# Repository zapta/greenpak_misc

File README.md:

# GreenPAKs
Everything related to Renesas GreenPAK programable logic devices.

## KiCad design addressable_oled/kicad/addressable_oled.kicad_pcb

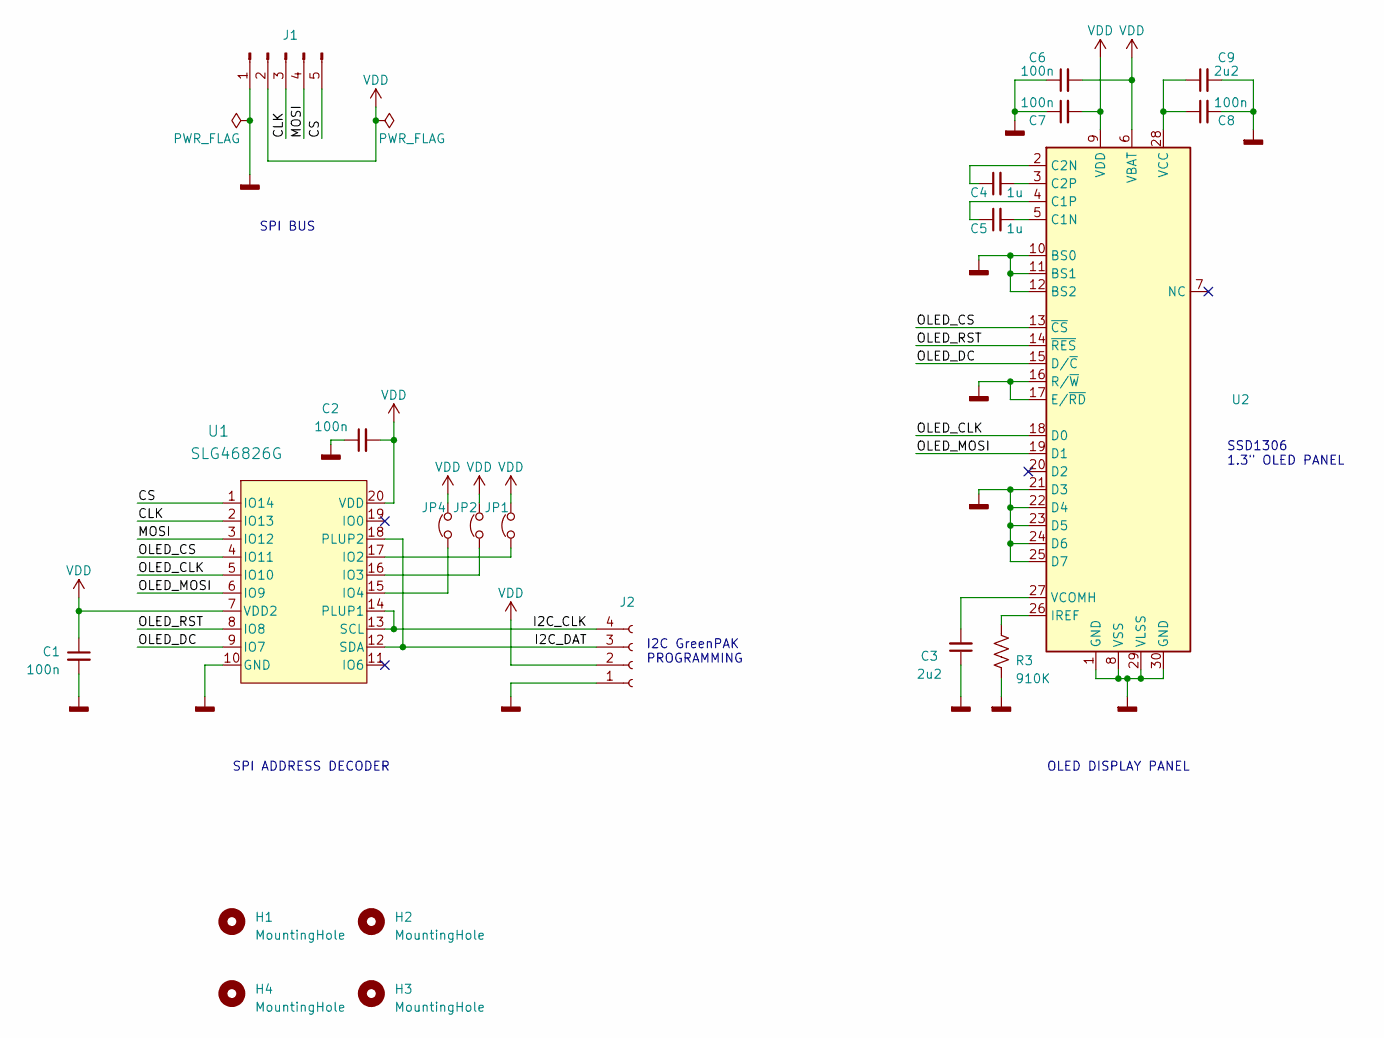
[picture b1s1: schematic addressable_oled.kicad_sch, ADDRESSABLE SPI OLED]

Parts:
C1, C2, C6, C7, C8: 100n; C_0603_1608Metric
C3, C9: 2u2; C_0603_1608Metric
C4, C5: 1u; C_0603_1608Metric
H1, H2, H3, H4: MountingHole
J1: Conn_01x05_Pin; PinHeader_1x05_P2.54mm_Vertical
J2: Conn_01x03_Socket; PinHeader_1x04_P2.54mm_Vertical
JP1, JP2, JP4: Jumper_2_Open; SolderJumper-2_P1.3mm_Open_Pad1.0x1.5mm
R3: 910K; R_0603_1608Metric
U1: SLG46826G; TSSOP20_MO-220_WECE_REN
U2: OLED-128O064D

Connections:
/CLK: J1.3, U1.2 (IO13)
/CS: J1.5, U1.1 (IO14)
/I2C_CLK: J2.4, U1.13 (SCL), U1.14 (PLUP1)
/I2C_DAT: J2.3, U1.12 (SDA), U1.18 (PLUP2)
/MOSI: J1.4, U1.3 (IO12)
/OLED_CLK: U1.5 (IO10), U2.18 (D0)
/OLED_CS: U1.4 (IO11), U2.13 (~CS)
/OLED_DC: U1.9 (IO7), U2.15 (D/~C)
/OLED_MOSI: U1.6 (IO9), U2.19 (D1)
/OLED_RST: U1.8 (IO8), U2.14 (~RES)
GND: C1.2, C2.1, C3.1, C6.1, C7.1, C8.2, C9.2, J1.1, J2.1, R3.2, U1.10 (GND), U2.1 (GND), U2.8 (VSS), U2.10 (BS0), U2.11 (BS1), U2.12 (BS2), U2.16 (R/~W), U2.17 (E/~RD), U2.21 (D3), U2.22 (D4), U2.23 (D5), U2.24 (D6), U2.25 (D7), U2.29 (VLSS), U2.30 (GND)
unnamed: JP1.1, U1.17 (IO2)
unnamed: JP2.1, U1.16 (IO3)
unnamed: JP4.1, U1.15 (IO4)
unnamed: C5.2, U2.5 (C1N)
unnamed: C5.1, U2.4 (C1P)
unnamed: C4.1, U2.2 (C2N)
unnamed: C4.2, U2.3 (C2P)
unnamed: R3.1, U2.26 (IREF)
unnamed: C8.1, C9.1, U2.28 (VCC)
unnamed: C3.2, U2.27 (VCOMH)
VDD: C1.1, C2.2, C6.2, C7.2, J1.2, J2.2, JP1.2, JP2.2, JP4.2, U1.7 (VDD2), U1.20 (VDD), U2.6 (VBAT), U2.9 (VDD)

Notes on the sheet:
SSD1306 1.3" OLED PANEL
I2C GreenPAK PROGRAMMING
SPI BUS
OLED DISPLAY PANEL
SPI ADDRESS DECODER

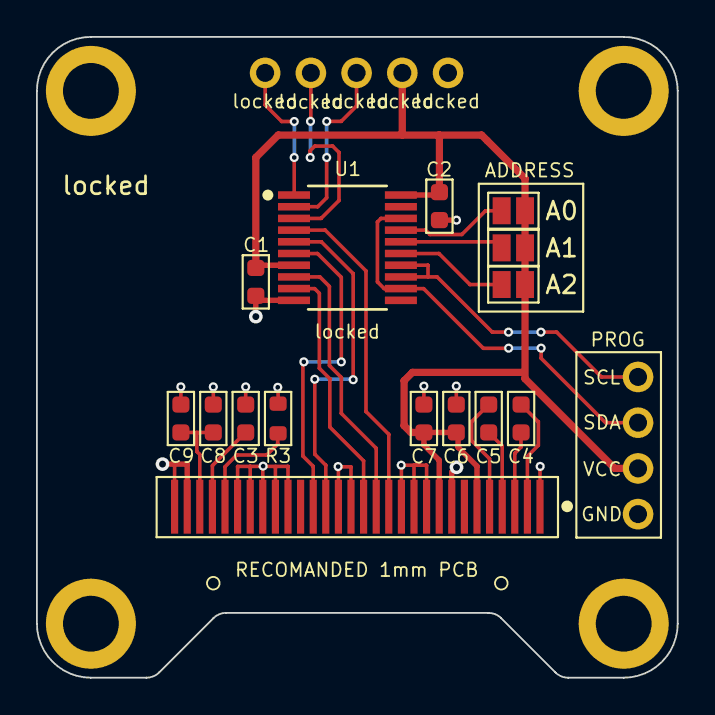
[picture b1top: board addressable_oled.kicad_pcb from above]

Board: 2 copper layers, 35.6 x 35.6 mm, 21 parts (0 on the bottom side), 22 nets.

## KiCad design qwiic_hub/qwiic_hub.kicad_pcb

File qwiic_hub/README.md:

# QWIIC I2C Hub

This little board provides a 1 to 4 fanout of QWIIC (I2C) connectors and allow to connect together multiple QWIIC boards such as the GreenPAK SMD adapters.

Item | Value | Comments
---|---|---
J1  |JST SH 1.0mm 4 Pos horizontal SMD | QWIIC input, from master.
J2- J5 |JST SH 1.0mm 4 Pos vertical SMD | QWIIC outputs, to slaves.
LED | Green LED  0603| Power indicator.
R | 3K - 7K 0603 resistor | LED current limiter.

<br>

<br>

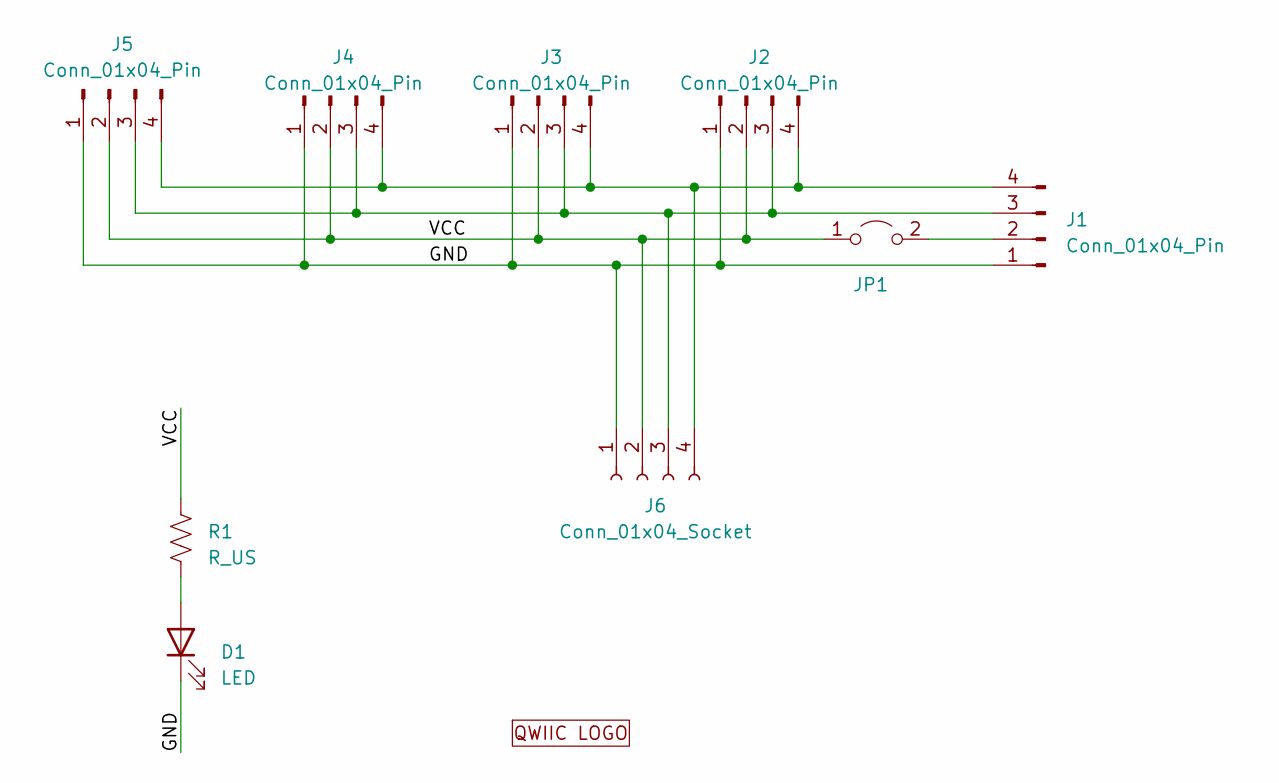
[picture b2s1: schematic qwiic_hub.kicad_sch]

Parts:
D1: LED; LED_0603_1608Metric
J1: Conn_01x04_Pin; JST_SH_SM04B-SRSS-TB_1x04-1MP_P1.00mm_Horizontal
J2, J3, J4, J5: Conn_01x04_Pin; JST_SH_BM04B-SRSS-TB_1x04-1MP_P1.00mm_Vertical
J6: Conn_01x04_Socket; PinHeader_1x04_P2.54mm_Vertical
JP1: Jumper_2_Open; SolderJumper-2_P1.3mm_Open_Pad1.0x1.5mm
R1: R_US; R_0402_1005Metric_Pad0.72x0.64mm_HandSolder
X1: QWIIC Logo; QWIIC_logo_10mm

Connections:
/GND: D1.1 (K), J1.1, J2.1, J3.1, J4.1, J5.1, J6.1
/VCC: J2.2, J3.2, J4.2, J5.2, J6.2, JP1.1 (A), R1.1
unnamed: D1.2 (A), R1.2
unnamed: J1.2, JP1.2 (B)
unnamed: J1.3, J2.3, J3.3, J4.3, J5.3, J6.3
unnamed: J1.4, J2.4, J3.4, J4.4, J5.4, J6.4

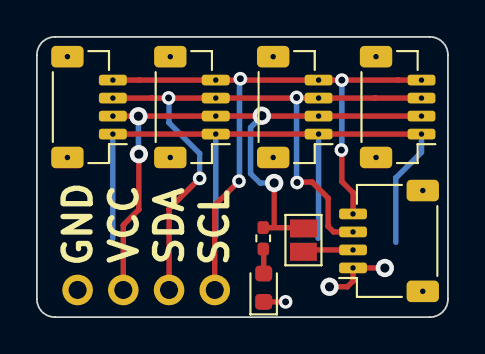
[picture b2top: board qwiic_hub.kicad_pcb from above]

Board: 2 copper layers, 22.8 x 15.6 mm, 10 parts (1 on the bottom side), 6 nets.

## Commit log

2023-12-01 Initial kicad version of smd_adapters. Needs cleanup.
2023-12-01 Cleaned up the GreenPAK TSSOP-20 smd adapter
2023-12-01 Added a sample design of an SPI address decoder.
2023-12-01 Renamed the smd adapters project.
2023-12-01 Cleaned up smd adapters directories.
2023-12-01 Fixed footprint library alias name.
2023-12-02 Completed the STQFN-24 greenpak smd adapter.
2023-12-02 Added pinout work in progress.
2023-12-02 Tweaked internal pullup/down resistors. Changed part number in pinout diagram to have the G extension.
2023-12-02 More progress on the TSQFN-20 smd adapter.
2023-12-03 More progress on the QFN-20 smd adapter.
2023-12-03 Completed the greenpak stqfn20 smd adapter.
2023-12-04 Adjusted the greenpak smd adaptres. Generated gerbers.
2023-12-04 Cleaned up greenpak smd adapters
2023-12-04 Updated greenpak smd adapter .png.
2023-12-04 Added gating of SCLK and MOSI
2023-12-05 Added a simple circuit for the glitch discussion.
2023-12-05 Added WaveDrop timing diagrams.
2023-12-06 Added pinout in png format.
2023-12-06 Renamed wavedrom files to .json.
2023-12-06 Tweaked timing diagrams.
2023-12-06 Added a readme file for the addressable SPI example.
2023-12-06 Tweaked readme.md.
2023-12-06 Fixed image reference in readme.md.
2023-12-06 Minor teadme.md fix.
2023-12-06 Minor readme.md tweak.
2023-12-06 MOved the addressable SPI directory.
2023-12-06 Tweaked readme.md
2023-12-06 Deleted unused images.
2023-12-06 Added a block diagram.
2023-12-06 MOSI out is not Z when CS_OUT is not active.
2023-12-06 Unify the timing diagrams.
2023-12-06 Changed the schematic from PNG to SVG.
2023-12-06 Flushing greenpak design changes.
2023-12-09 Added a blinky example
2023-12-09 Flushing blinky
2023-12-09 Renamed old blinky
2023-12-09 Added a blinky for the proper IC.
2023-12-10 Updated blinky files.
2023-12-10 Added docs directory
2023-12-10 Added pullup resistors to I2C signals.
2023-12-10 Changed i2C pullup resistors to 100k.
2023-12-10 Added a i2cdriver python skeleton
2023-12-10 Added user manual doc of the i2cmini
2023-12-10 Had progress on the i2C tool.
2023-12-11 Added a memory write method.
2023-12-11 Basic programming functionality is working.
2023-12-11 Cleaned up comments.
2023-12-11 Added two datasheets.
2023-12-11 Added test data file.
2023-12-11 Added functions to read/write config files.
2023-12-11 Updated programming capture file
2023-12-11 Added a workaround for reserved NVM bits and a method to reset the device.
2023-12-11 Renamed a directory
2023-12-11 Added better handling of non writeable NVM page.
2023-12-11 Cleaned up the operation waiting logic.
2023-12-11 Added method to scan the bus for devices.
2023-12-13 Skeleton for i2c pico.
2023-12-17 Added files for testing.
2023-12-17 Added code to dump generated bits.
2023-12-17 Added gitignore
2023-12-17 Consolidate doc directories
2023-12-19 Work in progress.
2023-12-20 Arduino serial bootloader works.
2023-12-20 Set up a skeleton with basic serial i/o.
2023-12-20 More progress with the pico i2c.
2023-12-20 More tweaks
2023-12-20 Deleted unused hidden arduino files.
2023-12-20 Dummy change for testing.
2023-12-21 Switched to the standard Arduino core.
2023-12-21 Cleaned up and added INFO command.
2023-12-21 Fixed a device address handling.
2023-12-22 Updated gitattributes.
2023-12-22 Added lib dependency on tinyusb
2023-12-22 Cleaned up old configuration.
2023-12-22 Added RPI Pico resources.
2023-12-22 Updated the Arduino driver installation instructions.
2023-12-22 Updated the installation notes.
2023-12-22 Updated the arduino driver notes
2023-12-22 Switched to standard Arduino USB/Serial
2023-12-22 Updated platformio.ini.
2023-12-22 Updated driver doc.
2023-12-22 Cleaned up platformio.ini
2023-12-22 Added a zadig screenshot
2023-12-22 Updated comment in platformio.ini, and deleted tools directory.
2023-12-22 Renamed i2c driver directory.
2023-12-22 Initial code of the i2c pico python driver.
2023-12-22 I2c pico read/write is working.
2023-12-22 Read/write to the device works.
2023-12-23 Cleaned up the pico driver protocol.
2023-12-23 i2c driver work in progress.
2023-12-23 Added errata file.
2023-12-23 Added a small test for page erasure
2023-12-23 Programming now works reliably.
2023-12-23 Added a TODO.
2023-12-23 Renamed 'tool' to 'driver'
2023-12-23 Cleaned up the directory structure.
2023-12-24 Flushing changes.
2023-12-25 Working in progress on the QWIIC greenpack adapter.
2023-12-25 Finalized the QWIIC adapter layout.
2023-12-25 Generated gerber files.
2023-12-25 Updated pcb images.
2023-12-26 Added experimental smd_adapters with tabs.
2023-12-29 Flushing pending changes.
2023-12-29 Added SMD adapter schematic. Cleaned up layout and panel.
2023-12-29 Cleaned up the schematic and layout.
2023-12-29 Tweaked the mouse bites.
2023-12-29 Generated gerbers
2023-12-30 Tweaked the layout.
2023-12-30 Generated gerbers.
2023-12-30 Updated gerber.
2023-12-30 Updated gerbers.
2023-12-30 Added an indication for JLCPCB that the connector is SMD. This should avoid the question about the pads which has holes for mechanical support and solder mask at the bottom.
2024-01-02 Added QWIIC logo.
2024-01-02 Refresh board renderings.
2024-01-03 Work in progress, 24 pin QWIIC adapter.
2024-01-03 More progress on the QFN footprint.
2024-01-03 Added the 24 pin footprints to the panel.
2024-01-03 Tweaked the SMD adapters
2024-01-03 Deleted old greenak footprints
2024-01-03 Updated smd_adapters directory to the design with tabs.
2024-01-03 Tweaked the VDD2 jumper
2024-01-03 Deleted old directories.
2024-01-04 Completed the qwiic hub layout
2024-01-04 Cleaned up the layout.
2024-01-05 Simplified the paneling: removed the horizontal tabs.
2024-01-05 Final verification and gerber generation.
2024-01-05 Tweaked the qwiic hub layout.
2024-01-10 First draft of i2c extender.
2024-01-11 More progress with the i2c extender.
2024-01-11 Tweaked the i2c_extender.
2024-01-11 I2C extender input pins tested successfuly.
2024-01-12 Renamed i2c_extener to io_extender. Minor cleanup.
2024-01-12 Added documentation
2024-01-12 Added python shell command to scripts.
2024-01-16 Added a readme file for the smd adapters
2024-01-16 Updatied PCB views.
2024-01-16 Updated the qwiic_hub image.
2024-01-16 Added QWIIC hub documentation.
2024-01-16 Updated doc.
2024-01-16 Fixed doc.
2024-01-19 Fixed MOSI out. Was tristate, now it's a regular output.
2024-01-19 Added a flasher script for the addresseable spi example.
2024-01-19 Changed address inputs to be all pullup.
2024-01-19 Added git attributes for crlf control.
2024-01-19 Added skeleton of addressable OLED example.
2024-01-20 Addressable OLED passes simulation.
2024-01-20 Minor tweak of labels.
2024-01-20 Updated flashers.
2024-01-20 Cleaned up addressable oled schematic.
2024-01-20 Addresable OLED passes a test with a logic analyzer.
2024-01-21 Fixed address matcher. Added CLK and MISO outputs.
2024-01-21 Addressable OLED demo works with a single screen.
2024-01-21 Initial version of Kicad project.
2024-01-21 Added docs.
2024-01-21 Work in progress. Added symbols and footprints.
2024-01-21 Work in progress. First pass of the schematic.
2024-01-21 More progress with the schematic and layout.
2024-01-21 Changed pin names.
2024-01-21 Schematic and layout in progress. Added GreenPAK pullup pins.
2024-01-22 More progress with the layout.
2024-01-22 Switched from kicad 7.0.1-0 to 7.0.10.
2024-01-22 Extended display pad from 2mm to 3mm.
2024-01-22 Final cleanup.
2024-01-22 Renamed addressable_oled to indicates it's obsolete. Project moved to greenpak_oled repository.
2024-01-23 First installment of the jig.
2024-01-23 More tweakes to the POGO design. Also, added a socket footprint.
2024-01-23 Added pogo socket symbol
2024-01-24 More progress with the Pogo layout.
2024-01-24 Removed old files that moved to a repository of their own.
2024-01-27 Fixed symbol pin name (SCL -> SDA)
2024-01-27 Removed projects that were moved to their own repository.
2024-01-30 Removed an obsolete file.
